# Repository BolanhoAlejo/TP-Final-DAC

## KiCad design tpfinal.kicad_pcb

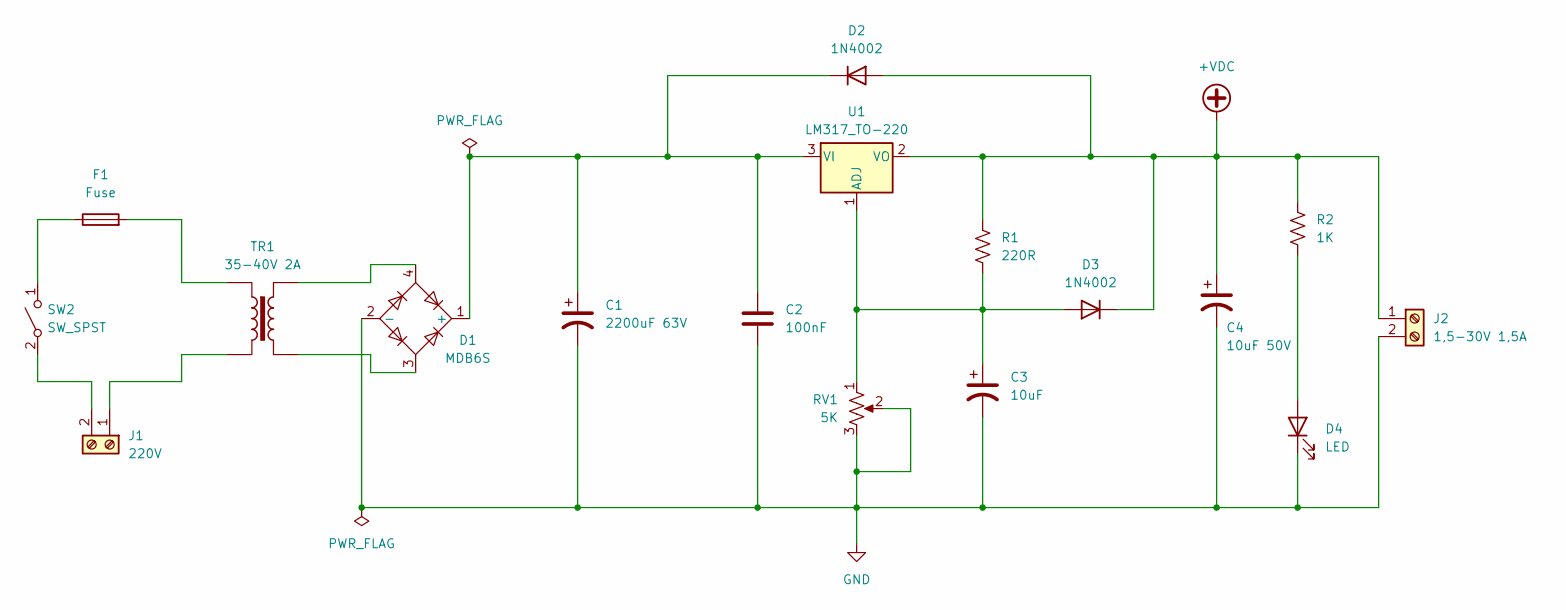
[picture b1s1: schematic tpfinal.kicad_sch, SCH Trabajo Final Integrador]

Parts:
C1: 2200uF 63V; CP_Radial_D10.0mm_P5.00mm
C2: 100nF; C_Disc_D5.0mm_W2.5mm_P2.50mm
C3: 10uF; CP_Radial_D5.0mm_P2.00mm
C4: 10uF 50V; CP_Radial_D5.0mm_P2.00mm
D1: MDB6S; Diode_Bridge_16.7x16.7x6.3mm_P10.8mm
D2, D3: 1N4002; D_DO-41_SOD81_P10.16mm_Horizontal
D4: LED; LED_D5.0mm_Horizontal_O3.81mm_Z9.0mm
F1: Fuse; Fuseholder_Cylinder-5x20mm_Schurter_0031_8201_Horizontal_Op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
J1: 220V; TerminalBlock_Phoenix_MKDS-1,5-2-5.08_1x02_P5.08mm_Horizont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
J2: 1,5-30V 1,5A; TerminalBlock_Phoenix_MKDS-1,5-2-5.08_1x02_P5.08mm_Horizont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
R1: 220R; R_Axial_DIN0207_L6.3mm_D2.5mm_P10.16mm_Horizontal
R2: 1K; R_Axial_DIN0207_L6.3mm_D2.5mm_P10.16mm_Horizontal
RV1: 5K; Potentiometer_Piher_T-16H_Single_Horizontal
SW2: SW_SPST; SW_E-Switch_EG1224_SPDT_Angled
TR1: 35-40V 2A; Transformer_Breve_TEZ-35x42
U1: LM317_TO-220; TO-220-3_Vertical

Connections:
+VDC: C4.1, D2.2 (A), D3.1 (K), J2.1, R1.1, R2.1, U1.2 (VO)
GND: C1.2, C2.2, C3.2, C4.2, D1.2 (-), D4.1 (K), J2.2, RV1.2, RV1.3
unnamed: C1.1, C2.1, D1.1 (+), D2.1 (K), U1.3 (VI)
unnamed: D1.3, TR1.5
unnamed: D1.4, TR1.4
unnamed: C3.1, D3.2 (A), R1.2, RV1.1, U1.1 (ADJ)
unnamed: D4.2 (A), R2.2
unnamed: F1.2, TR1.1
unnamed: J1.1, TR1.2
unnamed: J1.2, SW2.2 (A)
unnamed: F1.1, SW2.1 (B)

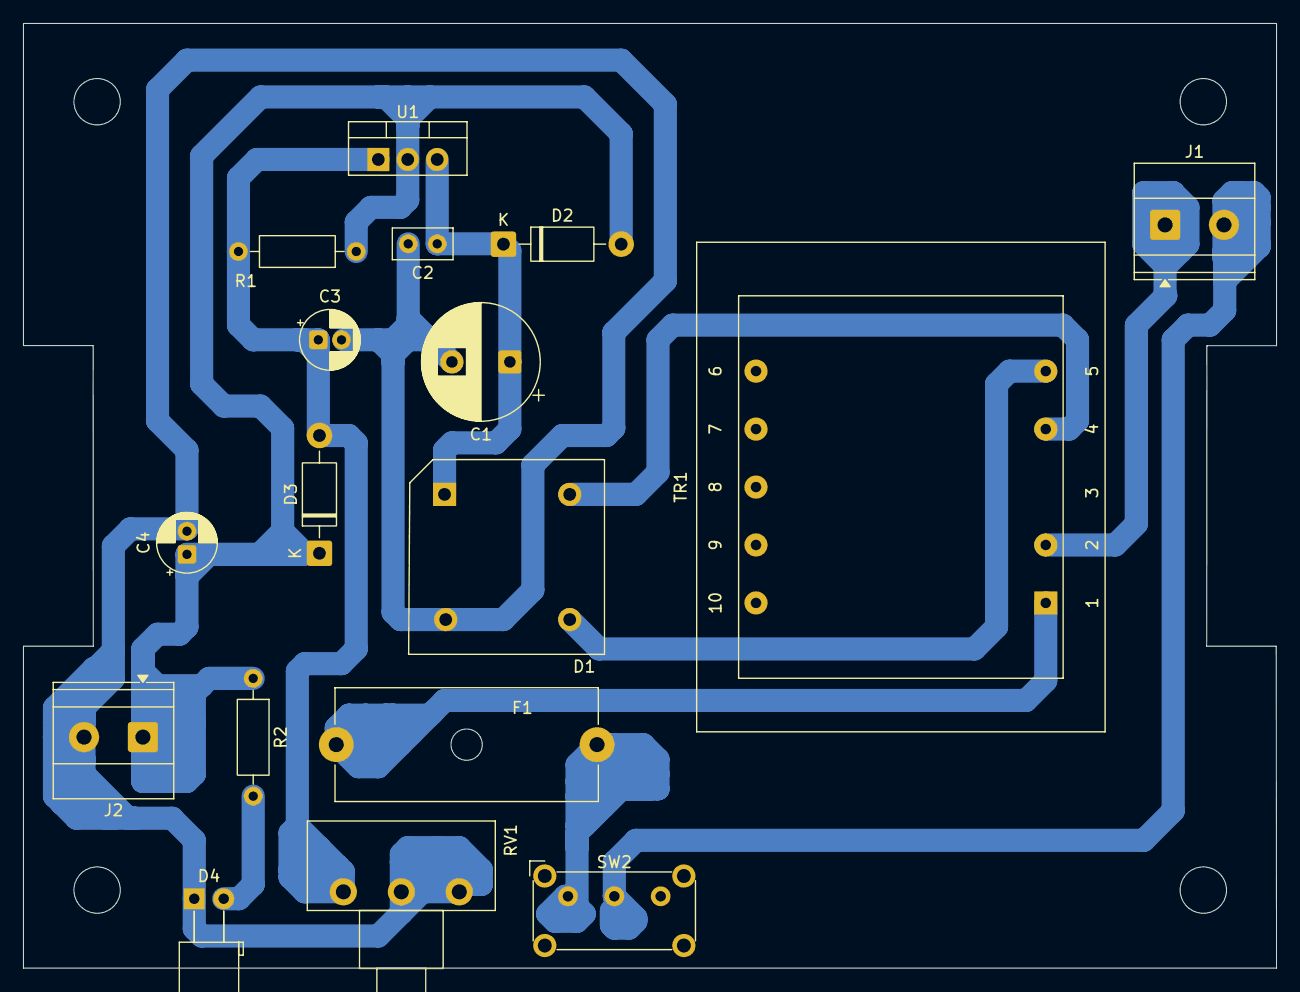
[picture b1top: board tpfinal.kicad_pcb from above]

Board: 2 copper layers, 108.1 x 81.5 mm, 17 parts (0 on the bottom side), 11 nets.

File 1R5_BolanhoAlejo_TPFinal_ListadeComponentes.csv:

"Reference","Qty","Value","DNP","Exclude from BOM","Exclude from Board","Footprint","Datasheet"
"C1","1","2200uF 63V","","","","Capacitor_THT:CP_Radial_D10.0mm_P5.00mm","~"
"C2","1","100nF","","","","Capacitor_THT:C_Disc_D5.0mm_W2.5mm_P2.50mm","~"
"C3","1","10uF","","","","Capacitor_THT:CP_Radial_D5.0mm_P2.00mm","~"
"C4","1","10uF 50V","","","","Capacitor_THT:CP_Radial_D5.0mm_P2.00mm","~"
"D1","1","MDB6S","","","","Diode_THT:Diode_Bridge_16.7x16.7x6.3mm_P10.8mm","https://www.onsemi.com/pub/Collateral/MDB8S-D.PDF"
"D2,D3","2","1N4002","","","","Diode_THT:D_DO-41_SOD81_P10.16mm_Horizontal","http://www.vishay.com/docs/88503/1n4001.pdf"
"D4","1","LED","","","","LED_THT:LED_D5.0mm_Horizontal_O3.81mm_Z9.0mm","~"
"F1","1","Fuse","","","","Fuse:Fuseholder_Cylinder-5x20mm_Schurter_0031_8201_Horizontal_Open","~"
"J1","1","220V","","","","TerminalBlock_Phoenix:TerminalBlock_Phoenix_MKDS-1,5-2-5.08_1x02_P5.08mm_Horizontal","~"
"J2","1","1,5-30V 1,5A","","","","TerminalBlock_Phoenix:TerminalBlock_Phoenix_MKDS-1,5-2-5.08_1x02_P5.08mm_Horizontal","~"
"R1","1","220R","","","","Resistor_THT:R_Axial_DIN0207_L6.3mm_D2.5mm_P10.16mm_Horizontal","~"
"R2","1","1K","","","","Resistor_THT:R_Axial_DIN0207_L6.3mm_D2.5mm_P10.16mm_Horizontal","~"
"RV1","1","5K","","","","Potentiometer_THT:Potentiometer_Piher_T-16H_Single_Horizontal","~"
"SW2","1","SW_SPST","","","","Button_Switch_THT:SW_E-Switch_EG1224_SPDT_Angled","~"
"TR1","1","35-40V 2A","","","","Transformer_THT:Transformer_Breve_TEZ-35x42",""
"U1","1","LM317_TO-220","","","","Package_TO_SOT_THT:TO-220-3_Vertical","http://www.ti.com/lit/ds/symlink/lm317.pdf"

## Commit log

2025-10-16 Fist-Commit
2025-10-25 Up-Exports
